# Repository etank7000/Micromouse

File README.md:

# Micromouse
UCLA IEEE Micromouse 2017-2018

To get the arm toolchain used in this repo, check out the following link and download the appropriate tar file. Be sure to read the included readme in the tar file as well.

https://developer.arm.com/open-source/gnu-toolchain/gnu-rm/downloads/7-2017-q4-major-1-1

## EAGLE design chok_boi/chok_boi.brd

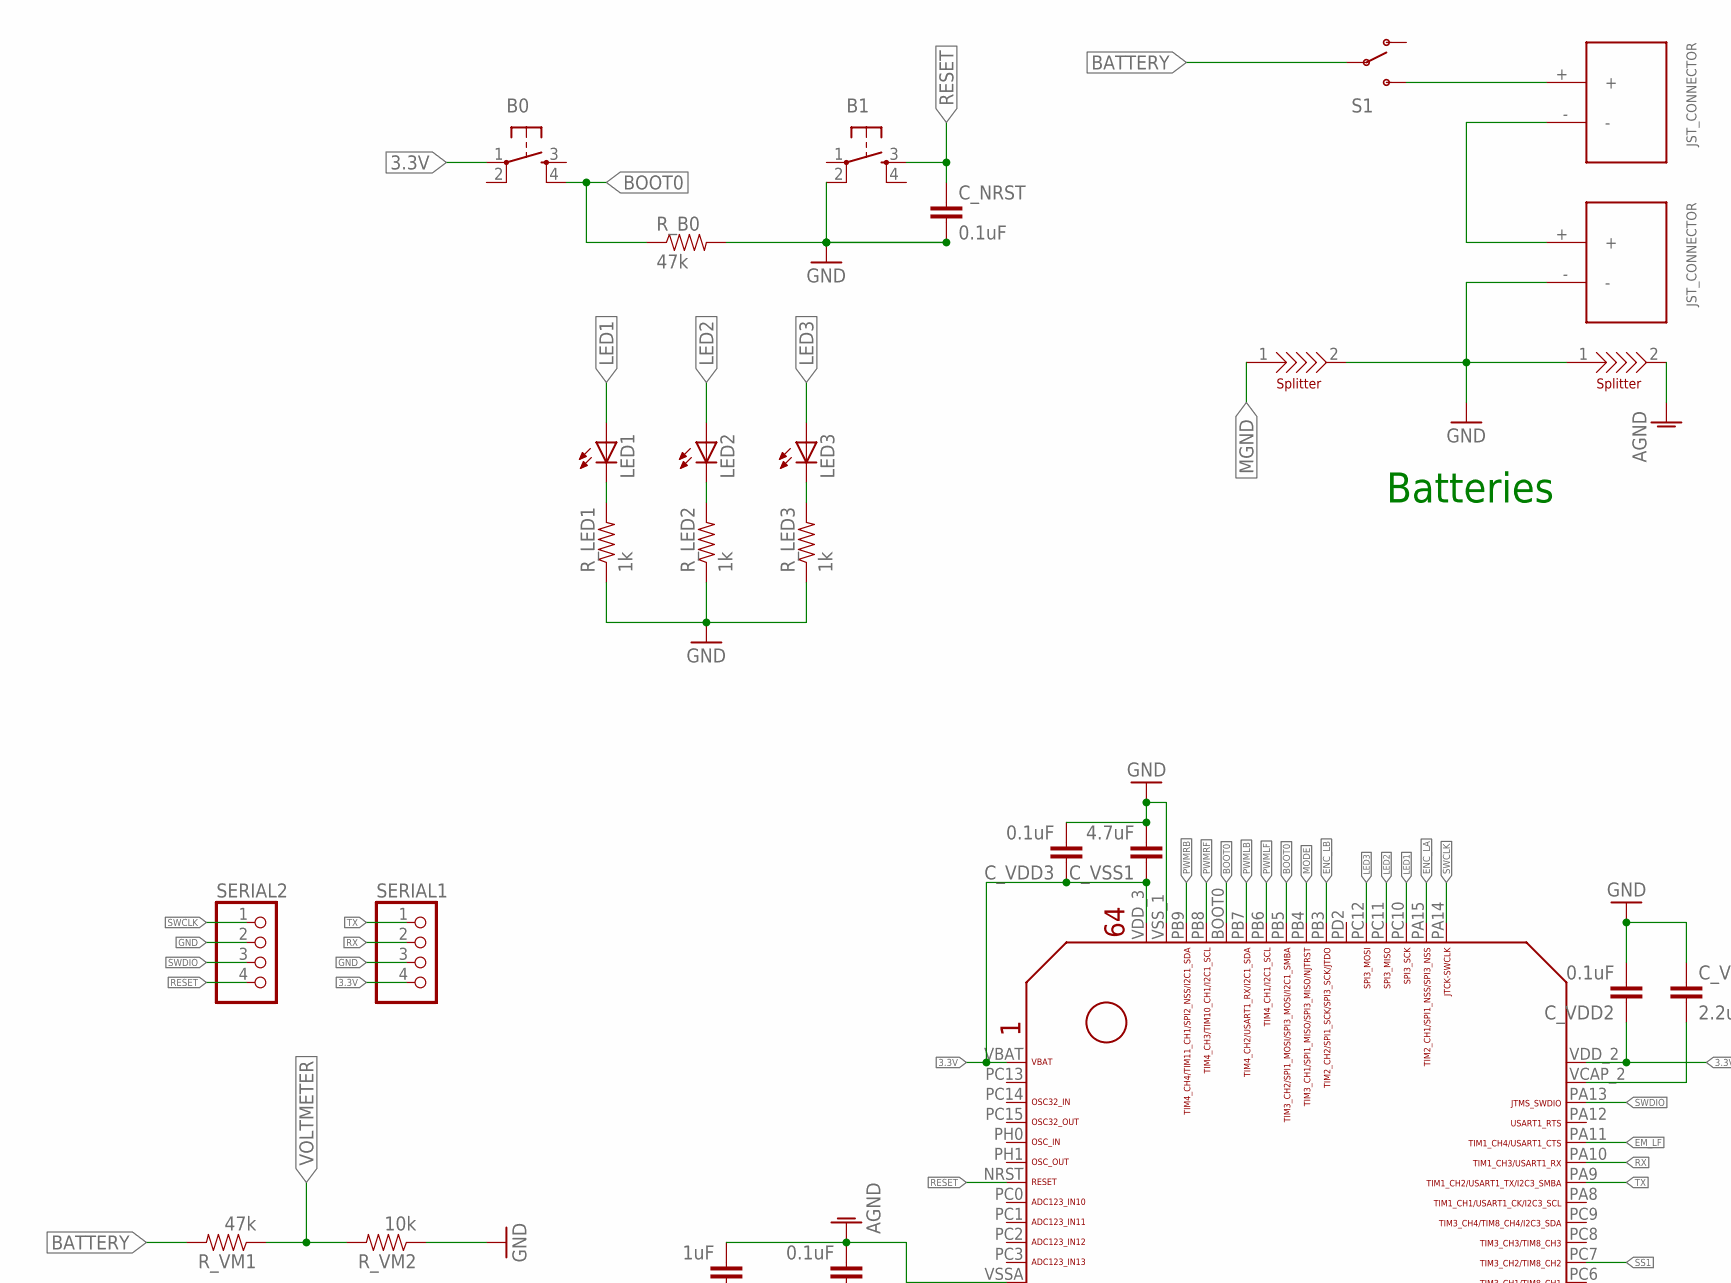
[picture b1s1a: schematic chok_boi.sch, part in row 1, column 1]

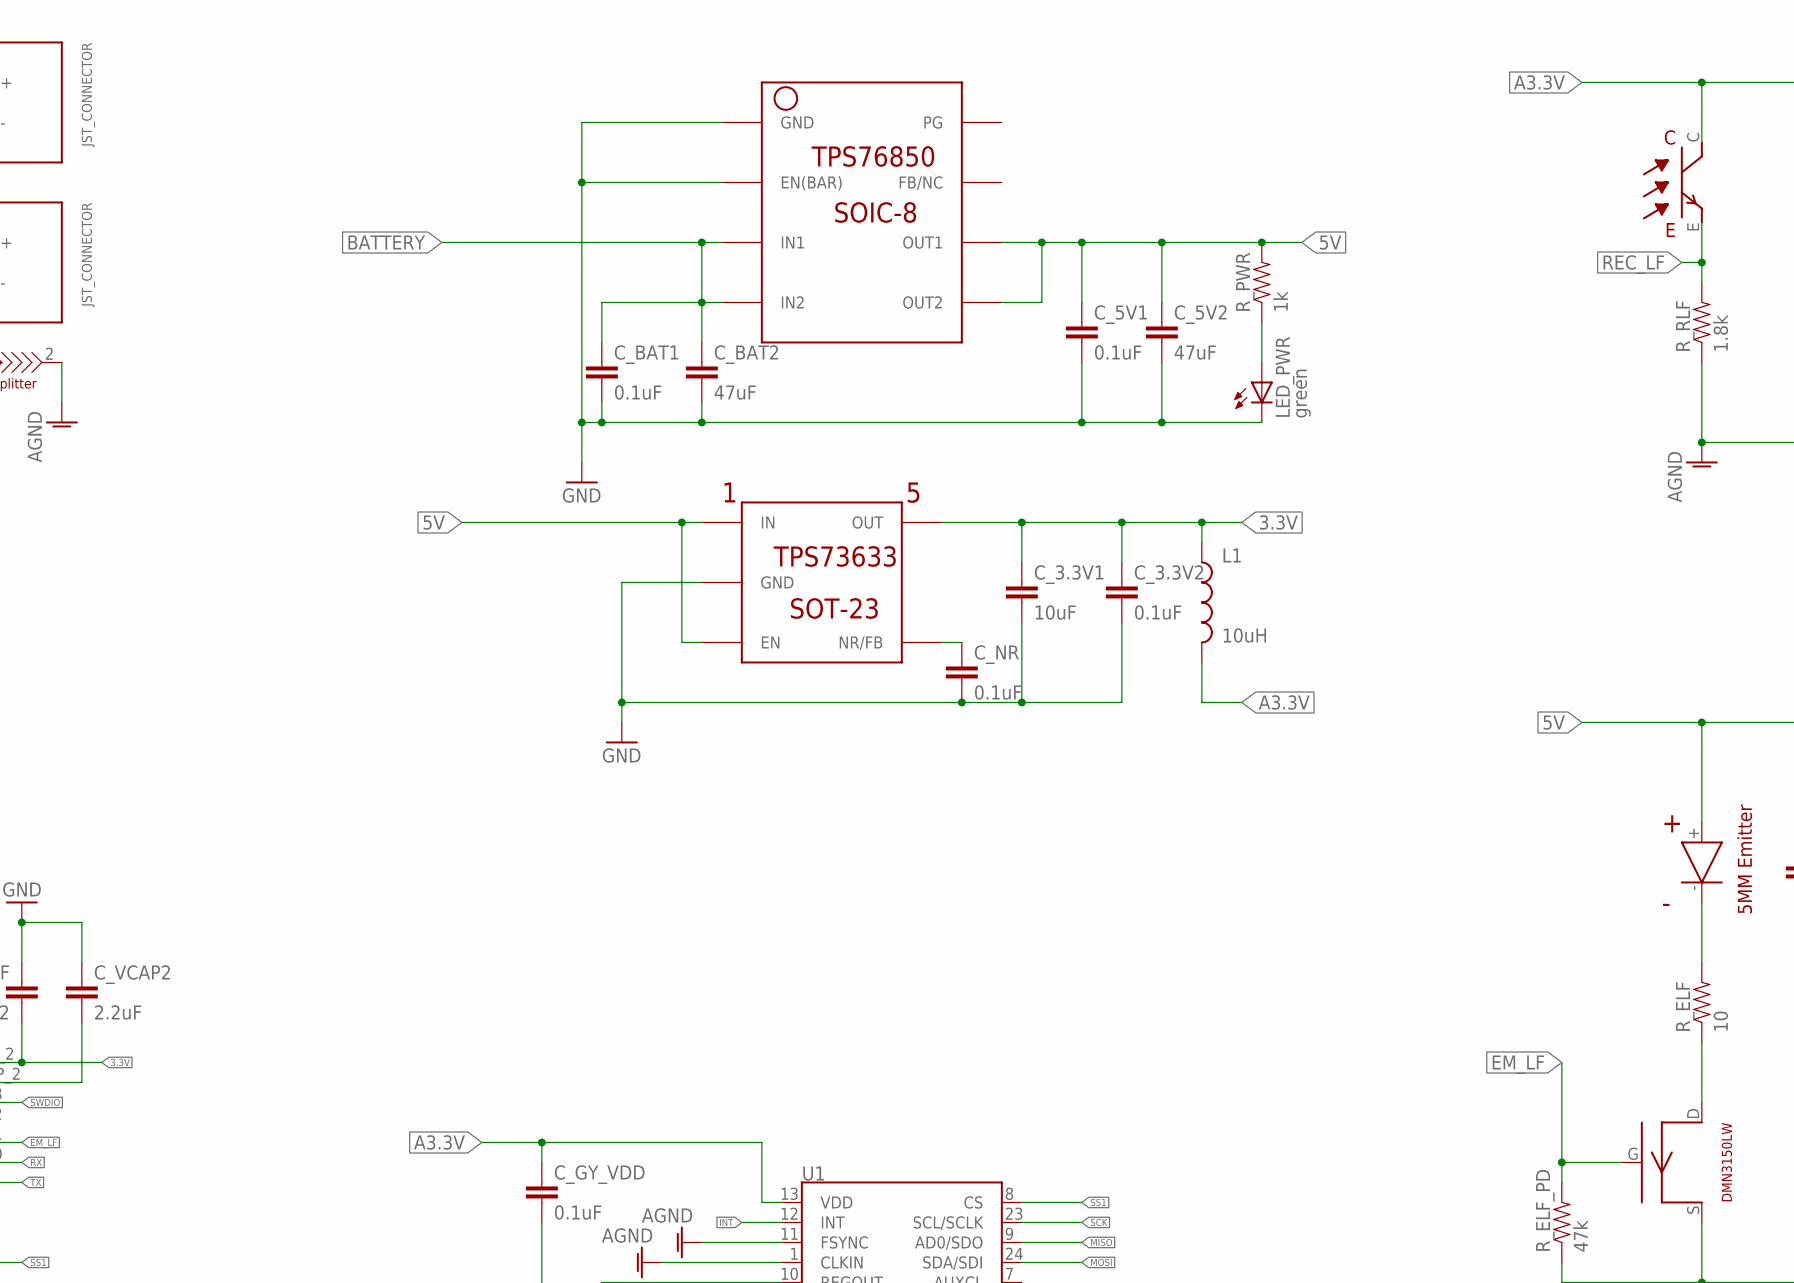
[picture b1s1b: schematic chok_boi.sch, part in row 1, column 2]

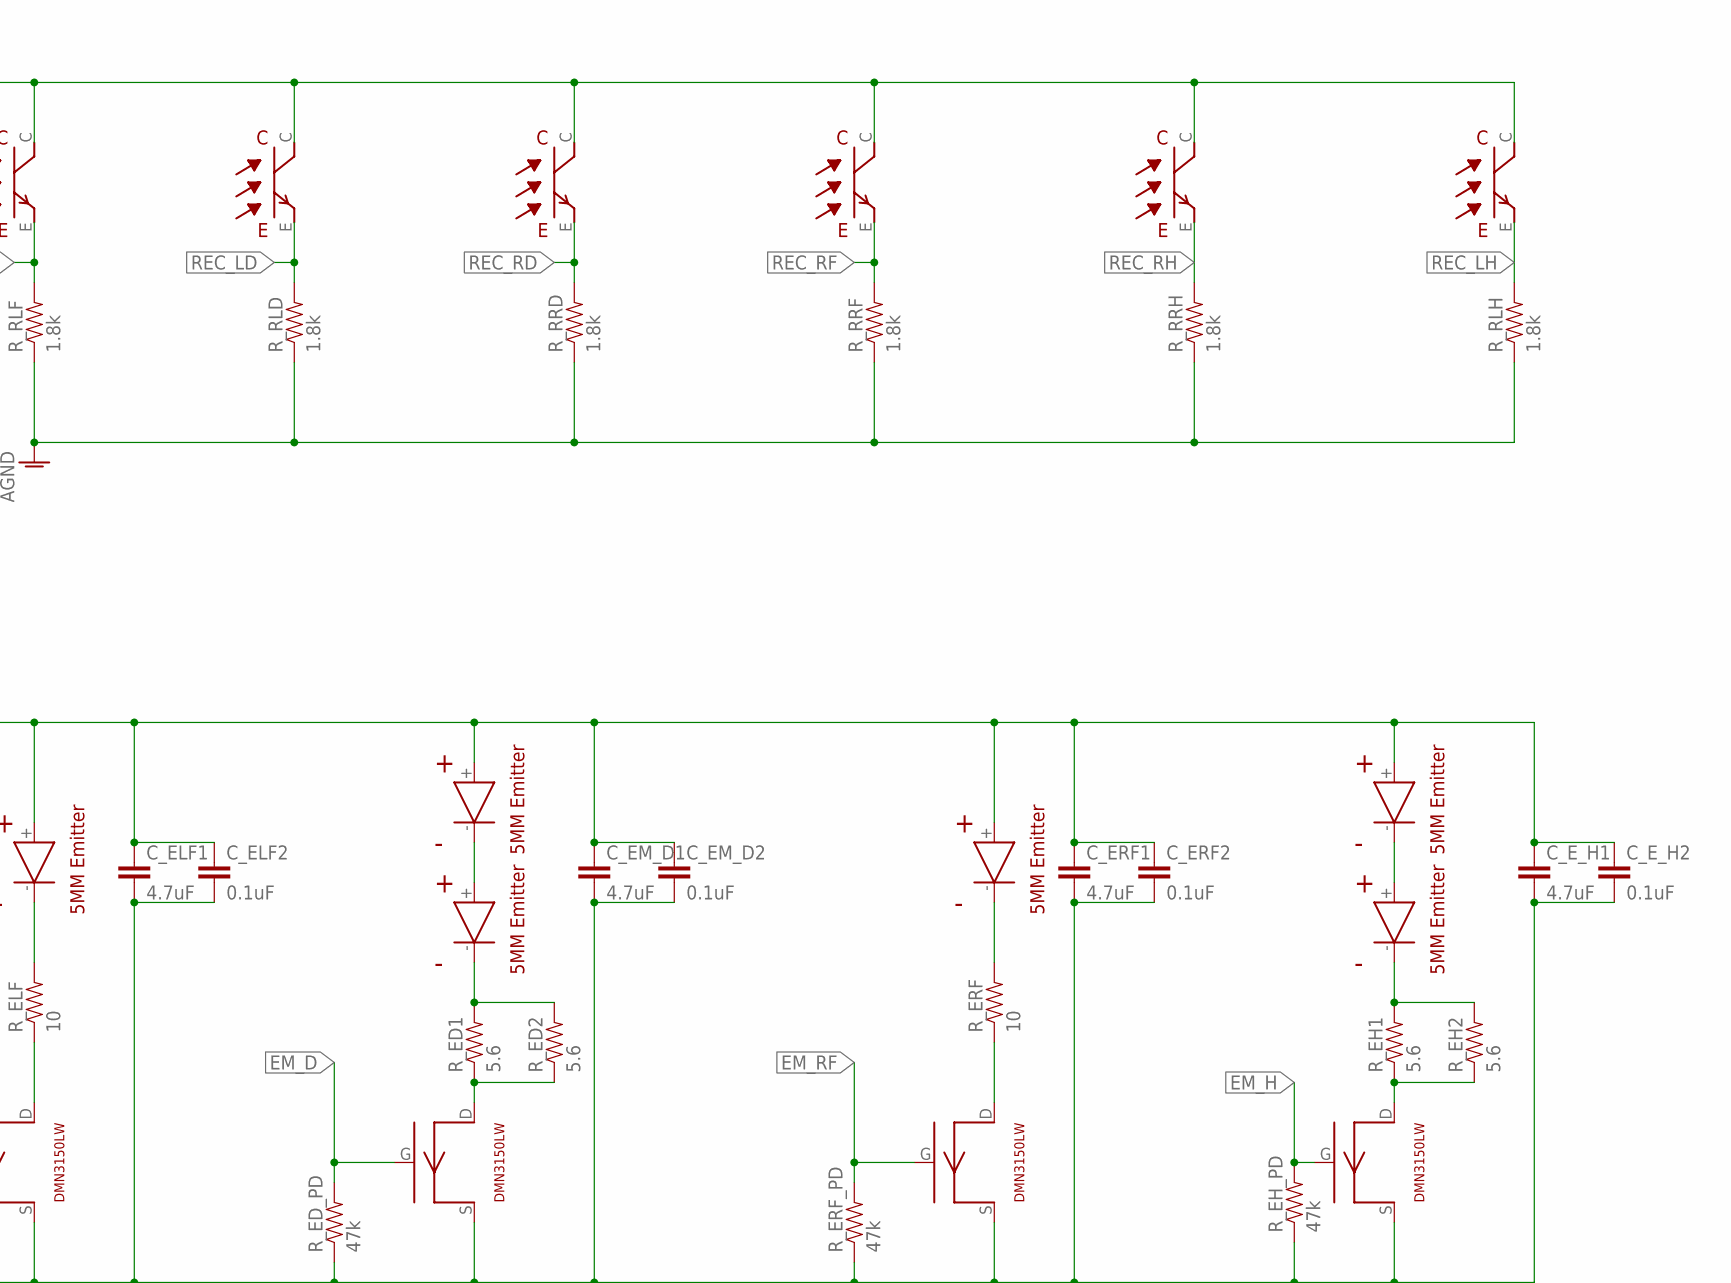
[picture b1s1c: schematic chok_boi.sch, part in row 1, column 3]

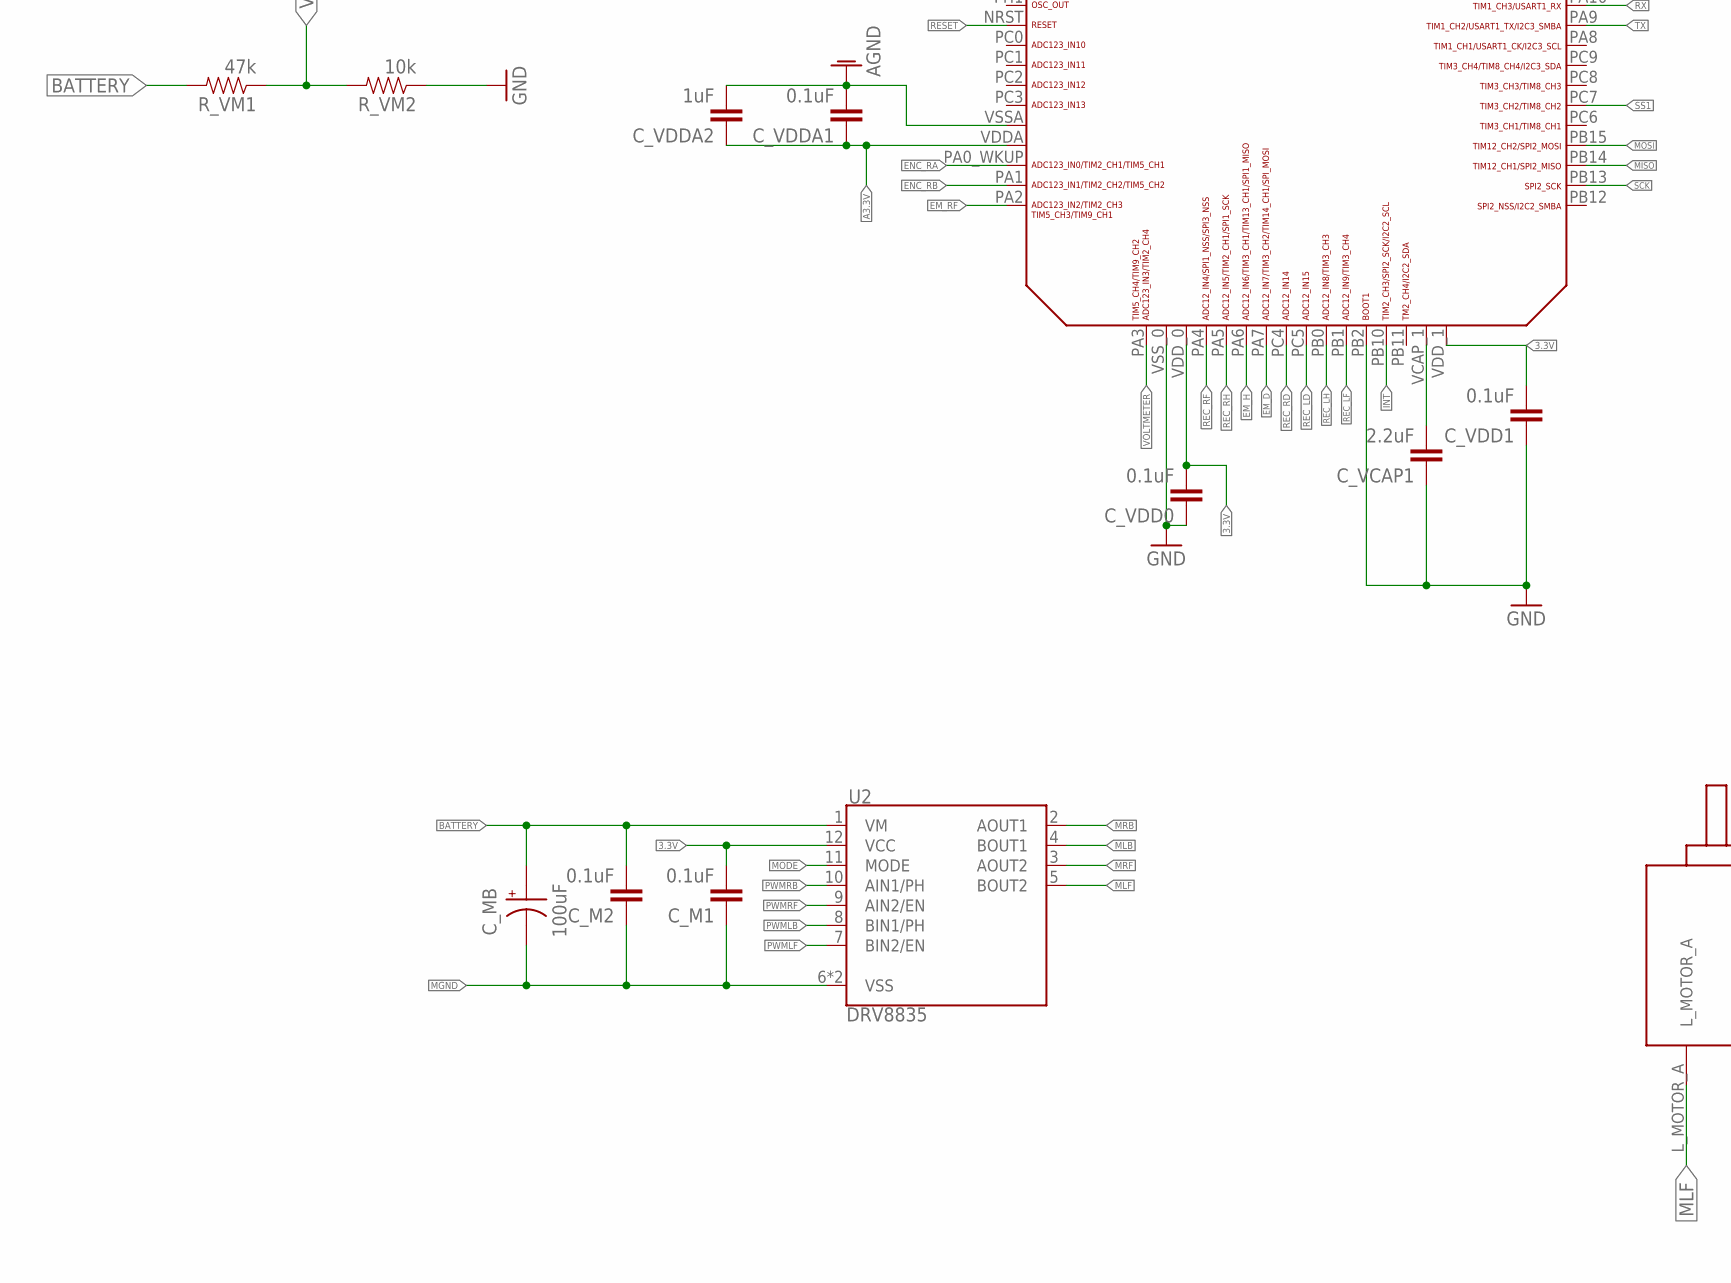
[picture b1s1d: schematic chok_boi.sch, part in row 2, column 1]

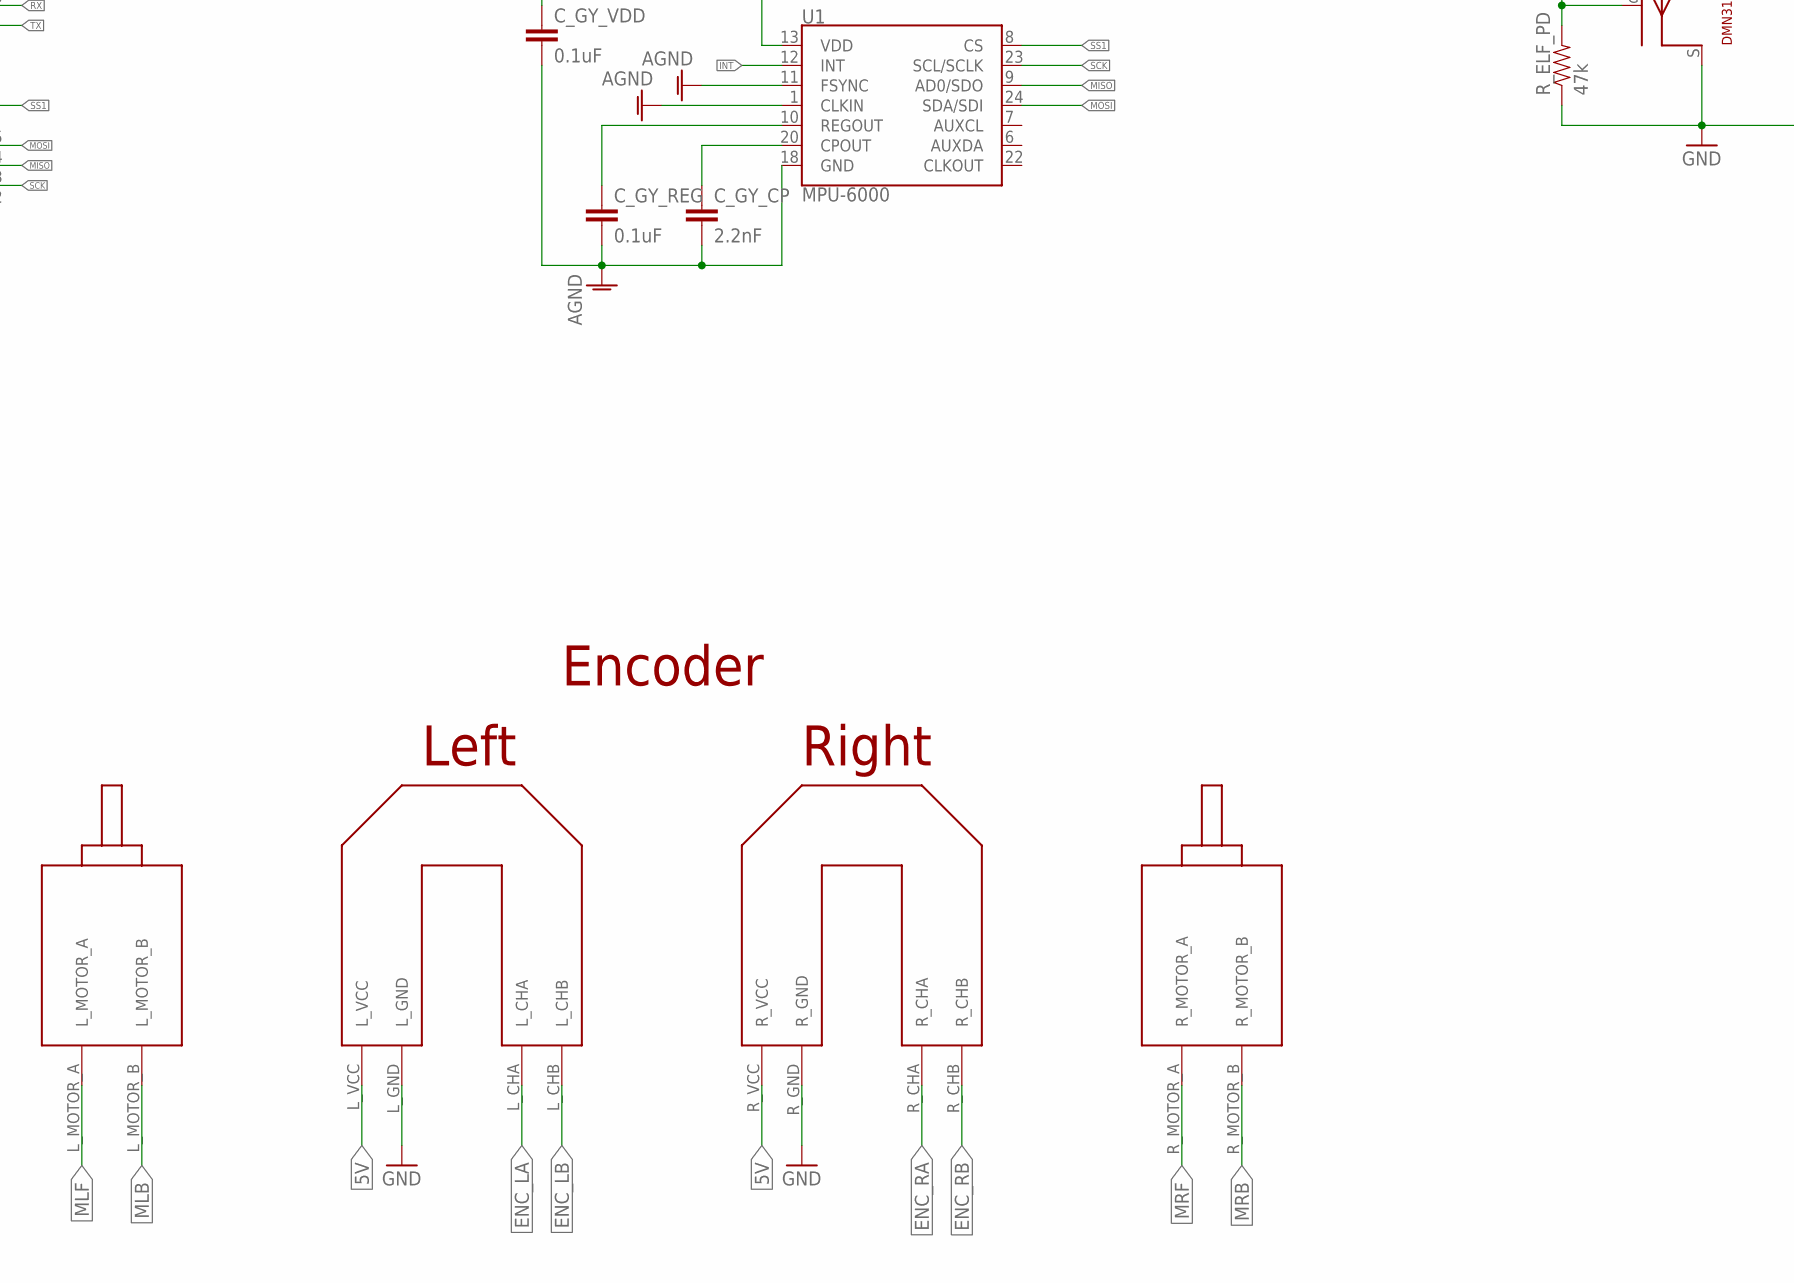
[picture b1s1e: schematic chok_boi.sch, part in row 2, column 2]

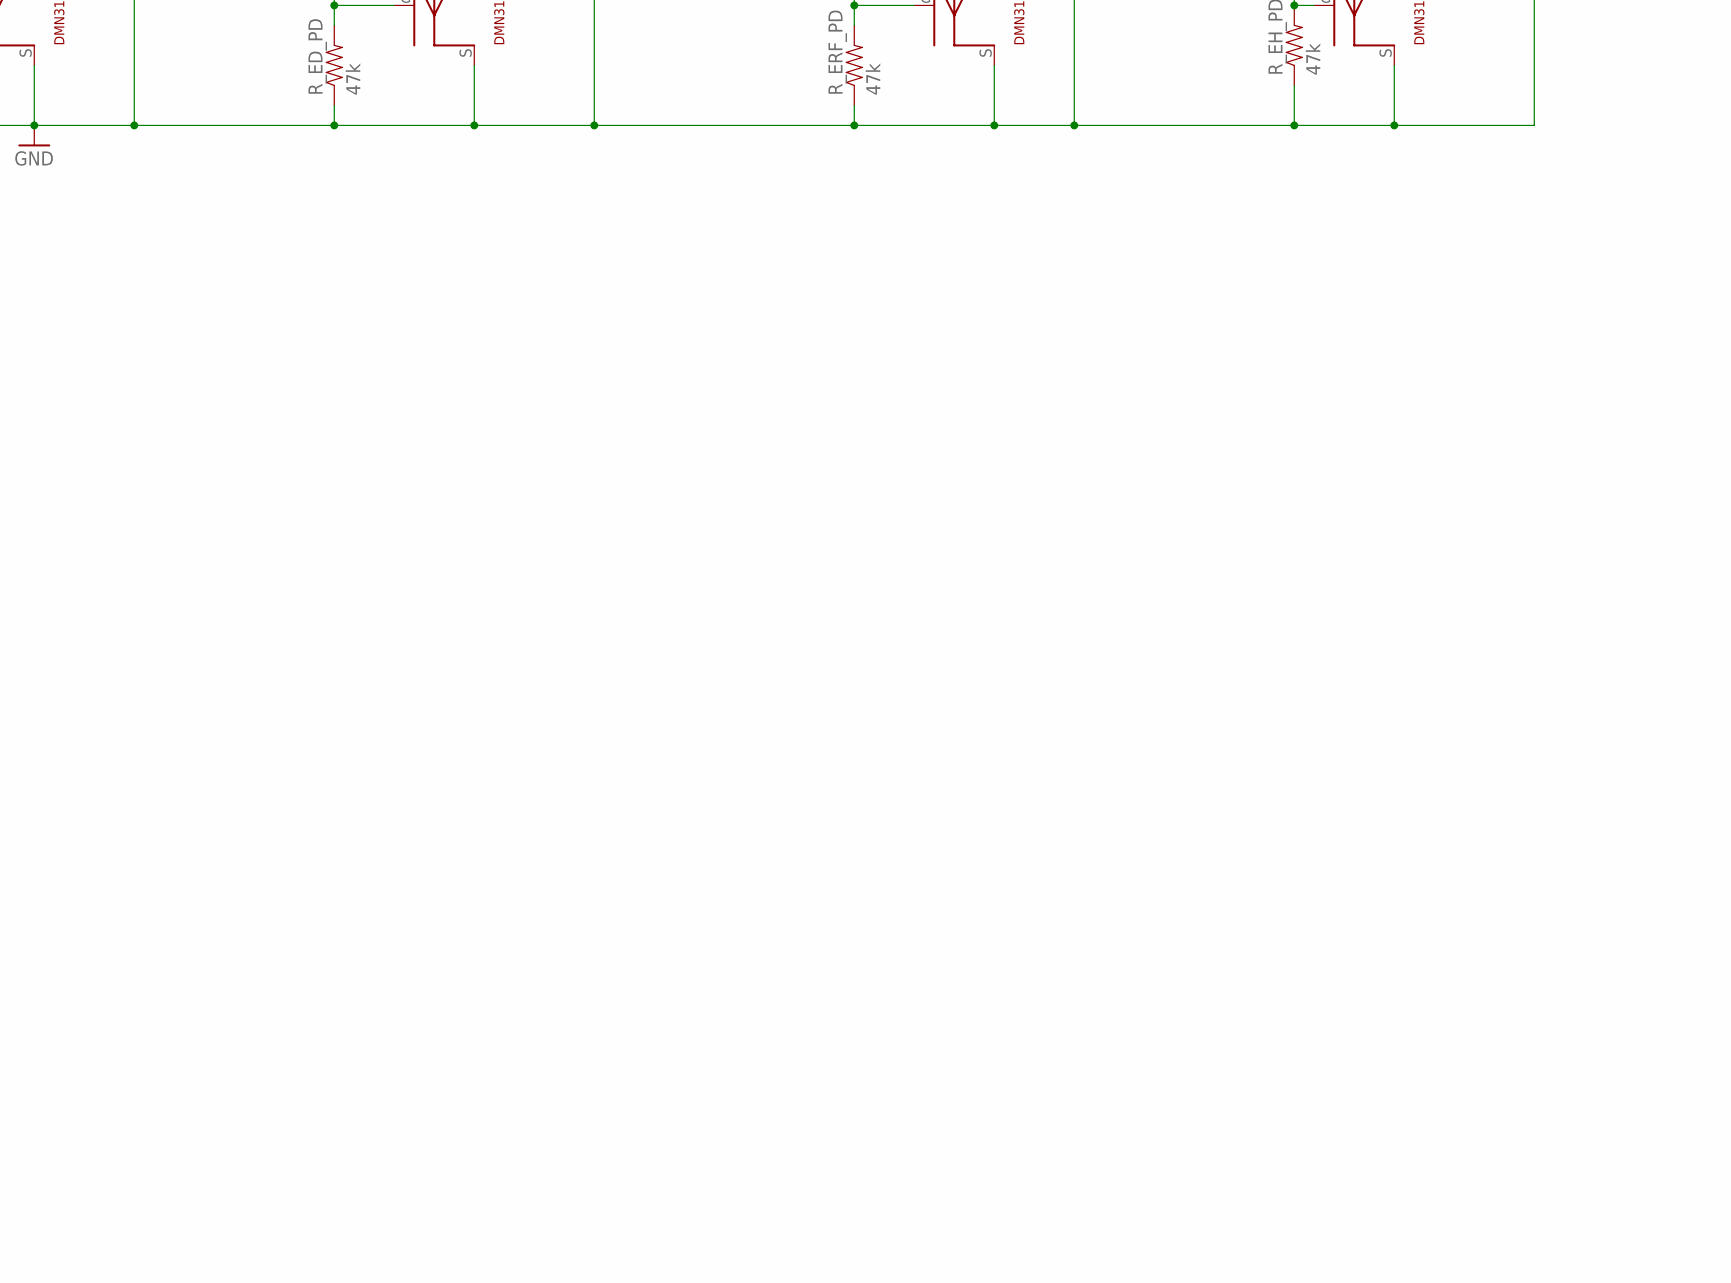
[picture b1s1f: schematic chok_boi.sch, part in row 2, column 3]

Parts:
B0, B1: TAC_SWITCHSMD; TACTILE-SWITCH-SMD
C_3.3V1: 10uF; 0603-CAP
C_3.3V2, C_5V1: 0.1uF; 0603-CAP
C_5V2: 47uF; 1210
C_BAT1: 0.1uF; 0603-CAP
C_BAT2: 47uF; 1210
C_ELF1: 4.7uF; 0603-CAP
C_ELF2: 0.1uF; 0603-CAP
C_EM_D1: 4.7uF; 0603-CAP
C_EM_D2: 0.1uF; 0603-CAP
C_ERF1: 4.7uF; 0603-CAP
C_ERF2: 0.1uF; 0603-CAP
C_E_H1: 4.7uF; 0603-CAP
C_E_H2: 0.1uF; 0603-CAP
C_GY_CP: 2.2nF; 0603-CAP
C_GY_REG: 0.1uF; 0603-CAP
C_GY_VDD: 0.1uF; 0603-CAP
C_M1, C_M2: 0.1uF; 0603-CAP
C_MB: 100uF; X
C_NR: 0.1uF; 0603-CAP
C_NRST: 0.1uF; 0603-CAP
C_VCAP1, C_VCAP2: 2.2uF; 0603-CAP
C_VDD0, C_VDD1, C_VDD2, C_VDD3: 0.1uF; 0603-CAP
C_VDDA1: 0.1uF; 0603-CAP
C_VDDA2: 1uF; 0603-CAP
C_VSS1: 4.7uF; 0603-CAP
L1: 10uH; 1007
LED1, LED2, LED3: LED0603; LED-0603
LED_PWR: green; LED-1206
LEFT_FRONT_EMITTER: EMITTER
NMOS1, NMOS2, NMOS3, NMOS4: DMN3150LW
REC_LF: RECEIVER
R_B0: 47k; 0603-RES
R_ED1, R_ED2: 5.6; 0603-RES
R_ED_PD: 47k; 0603-RES
R_EH1, R_EH2: 5.6; 0603-RES
R_EH_PD: 47k; 0603-RES
R_ELF: 10; 0603-RES
R_ELF_PD: 47k; 0603-RES
R_ERF: 10; 0603-RES
R_ERF_PD: 47k; 0603-RES
R_LED1, R_LED2, R_LED3: 1k; 0603-RES
R_PWR: 1k; 0603-RES
R_RLD: 1.8k; 0603-RES
R_RLF: 1.8k; 0603-RES
R_RLH: 1.8k; 0603-RES
R_RRD: 1.8k; 0603-RES
R_RRF: 1.8k; 0603-RES
R_RRH: 1.8k; 0603-RES
R_VM1: 47k; 0603-RES
R_VM2: 10k; 0603-RES
S1: SWITCH-SPSTPTH; SWITCH-SPDT
SERIAL1, SERIAL2: PINHD-1X4; 1X04
U1: MPU-6000; QFN-24-EP
U2: DRV8835; WSON-12
U$1, U$2: JST_CONNECTOR_FEMALE
U$3: TPS73633(SOT-23)
U$4: TPS76850(SOIC-8)
U$5: STM32F405/415_LQFP64
U$7, U$8, U$9, U$20, U$21: RECEIVER
U$11, U$13, U$17, U$18, U$19: EMITTER
U$12: FUTURA_V1.0_MOTOR_MOUNT; FUTURA_V1.0_MOTOT_MOUNT
U$15, U$16: SPLITTER

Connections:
3.3V: B0.1, C_3.3V1.1, C_3.3V2.1, C_M1.2, C_VDD0.2, C_VDD1.2, C_VDD2.1, C_VDD3.1, C_VSS1.1, L1.1, SERIAL1.4, U2.12 (VCC), U$3.OUT, U$5.VBAT, U$5.VDD_0, U$5.VDD_1, U$5.VDD_2, U$5.VDD_3
5V: C_5V1.1, C_5V2.1, C_ELF1.1, C_ELF2.1, C_EM_D1.1, C_EM_D2.1, C_ERF1.1, C_ERF2.1, C_E_H1.1, C_E_H2.1, LEFT_FRONT_EMITTER.+, R_PWR.2, U$3.EN, U$3.IN, U$4.OUT1, U$4.OUT2, U$11.+, U$12.L_VCC, U$12.R_VCC, U$13.+, U$18.+
A3.3V: C_GY_VDD.1, C_VDDA1.1, C_VDDA2.1, L1.2, REC_LF.C, U1.13 (VDD), U$5.VDDA, U$7.C, U$8.C, U$9.C, U$20.C, U$21.C
AGND: C_GY_CP.2, C_GY_REG.2, C_GY_VDD.2, C_VDDA1.2, C_VDDA2.2, R_RLD.1, R_RLF.1, R_RLH.1, R_RRD.1, R_RRF.1, R_RRH.1, U1.1 (CLKIN), U1.11 (FSYNC), U1.18 (GND), U$5.VSSA, U$15.2
BATTERY: C_BAT1.1, C_BAT2.1, C_M2.2, C_MB.A, R_VM1.2, S1.2, U2.1 (VM), U$4.IN1, U$4.IN2
BOOT0: B0.4, R_B0.1, U$5.BOOT0, U$5.PB5
D2_EM: R_ED1.2, R_ED2.2, U$17.-
D_EM: U$11.-, U$17.+
EM_D: NMOS2.G, R_ED_PD.2, U$5.PA7
EM_H: NMOS4.G, R_EH_PD.2, U$5.PA6
EM_LF: NMOS1.G, R_ELF_PD.2, U$5.PA11
EM_RF: NMOS3.G, R_ERF_PD.2, U$5.PA2
ENC_LA: U$5.PA15, U$12.L_CHA
ENC_LB: U$5.PB3, U$12.L_CHB
ENC_RA: U$5.PA0_WKUP (PA0_AKUP), U$12.R_CHA
ENC_RB: U$5.PA1, U$12.R_CHB
GND: B1.2, C_3.3V1.2, C_3.3V2.2, C_5V1.2, C_5V2.2, C_BAT1.2, C_BAT2.2, C_ELF1.2, C_ELF2.2, C_EM_D1.2, C_EM_D2.2, C_ERF1.2, C_ERF2.2, C_E_H1.2, C_E_H2.2, C_NR.2, C_NRST.2, C_VCAP1.1, C_VCAP2.1, C_VDD0.1, C_VDD1.1, C_VDD2.2, C_VDD3.2, C_VSS1.2, LED_PWR.C, NMOS1.S, NMOS2.S, NMOS3.S, NMOS4.S, R_B0.2, R_ED_PD.1, R_EH_PD.1, R_ELF_PD.1, R_ERF_PD.1, R_LED1.1, R_LED2.1, R_LED3.1, R_VM2.1, SERIAL1.3, SERIAL2.2, U$1.-, U$3.GND, U$4.EN(BAR), U$4.GND, U$5.PB2, U$5.VSS_0, U$5.VSS_1, U$12.L_GND, U$12.R_GND, U$15.1, U$16.2
H2_EM: R_EH1.2, R_EH2.2, U$19.-
H_EM: U$18.-, U$19.+
INT: U1.12 (INT), U$5.PB10
LED1: LED1.A, U$5.PC10
LED2: LED2.A, U$5.PC11
LED3: LED3.A, U$5.PC12
LF_EM: LEFT_FRONT_EMITTER.-, R_ELF.2
MGND: C_M1.1, C_M2.1, C_MB.C, U2.6 (VSS), U2.PAD (VSS), U$16.1
MISO: U1.9 (AD0/SDO), U$5.PB14
MLB: U2.4 (BOUT1), U$12.L_MOTOR_B
MLF: U2.5 (BOUT2), U$12.L_MOTOR_A
MODE: U2.11 (MODE), U$5.PB4
MOSI: U1.24 (SDA/SDI), U$5.PB15
MRB: U2.2 (AOUT1), U$12.R_MOTOR_B
MRF: U2.3 (AOUT2), U$12.R_MOTOR_A
unnamed: U$1.+, U$2.-
unnamed: S1.3 (S), U$2.+
unnamed: C_NR.1, U$3.NR/FB
unnamed: C_VCAP1.2, U$5.VCAP_1
unnamed: NMOS3.D, R_ERF.1
unnamed: C_VCAP2.2, U$5.VCAP_2
unnamed: NMOS1.D, R_ELF.1
unnamed: LED_PWR.A, R_PWR.1
unnamed: LED1.C, R_LED1.2
unnamed: LED2.C, R_LED2.2
unnamed: NMOS2.D, R_ED1.1, R_ED2.1
unnamed: NMOS4.D, R_EH1.1, R_EH2.1
unnamed: C_GY_REG.1, U1.10 (REGOUT)
unnamed: LED3.C, R_LED3.2
unnamed: C_GY_CP.1, U1.20 (CPOUT)
PWMLB: U2.8 (BIN1/PH), U$5.PB7
PWMLF: U2.7 (BIN2/EN), U$5.PB6
PWMRB: U2.10 (AIN1/PH), U$5.PB9
PWMRF: U2.9 (AIN2/EN), U$5.PB8
REC_LD: R_RLD.2, U$5.PC5, U$7.E
REC_LF: REC_LF.E, R_RLF.2, U$5.PB1
REC_LH: R_RLH.2, U$5.PB0, U$21.E
REC_RD: R_RRD.2, U$5.PC4, U$8.E
REC_RF: R_RRF.2, U$5.PA4, U$9.E
REC_RH: R_RRH.2, U$5.PA5, U$20.E
RESET: B1.3, C_NRST.1, SERIAL2.4, U$5.NRST
RF_EM: R_ERF.2, U$13.-
RX: SERIAL1.2, U$5.PA10
SCK: U1.23 (SCL/SCLK), U$5.PB13
SS1: U1.8 (CS), U$5.PC7
SWCLK: SERIAL2.1, U$5.PA14
SWDIO: SERIAL2.3, U$5.PA13
TX: SERIAL1.1, U$5.PA9
VOLTMETER: R_VM1.1, R_VM2.2, U$5.PA3

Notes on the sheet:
Batteries

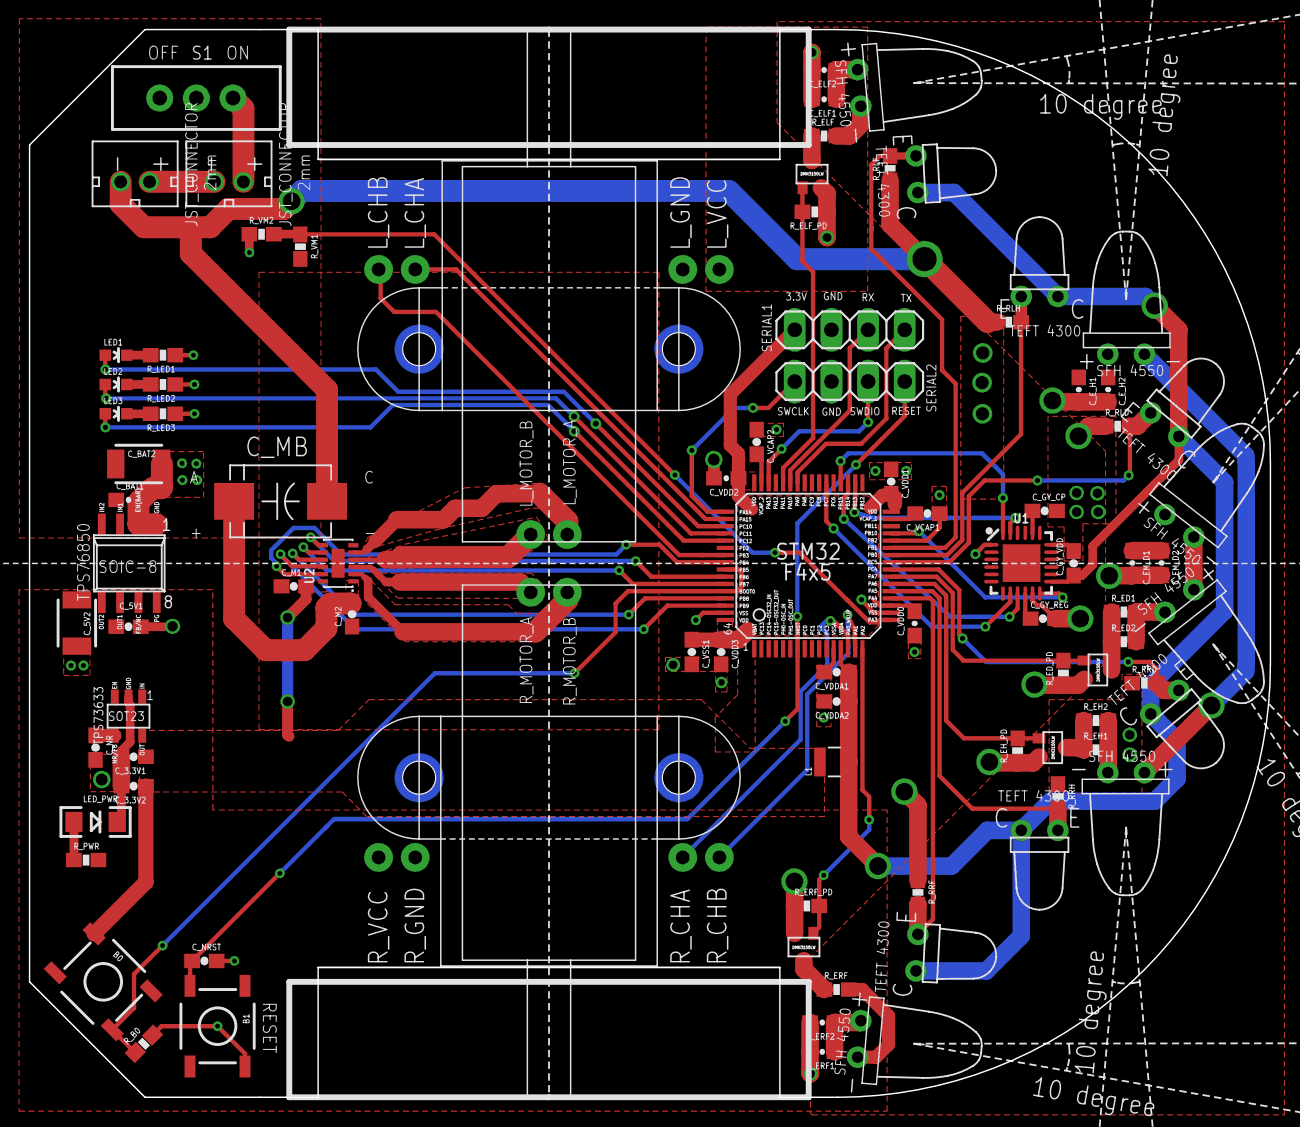
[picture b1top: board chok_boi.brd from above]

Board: 2 copper layers, 86.0 x 74.0 mm, 90 parts (0 on the bottom side), 66 nets.

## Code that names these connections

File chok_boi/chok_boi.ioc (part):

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Mcu.Name=STM32F405RGTx
Mcu.Package=LQFP64
Mcu.UserName=STM32F405RGTx
PA0-WKUP.GPIOParameters=GPIO_Label
PA0-WKUP.GPIO_Label=ENC_RA
PA0-WKUP.Signal=S_TIM5_CH1
PA1.GPIOParameters=GPIO_Label
PA1.GPIO_Label=ENC_RB
PA1.Signal=S_TIM5_CH2
PA10.Mode=Asynchronous
PA10.Signal=USART1_RX
PA11.GPIOParameters=GPIO_Label
PA11.GPIO_Label=EM_LF
PA11.Signal=GPIO_Output
PA13.Mode=Serial_Wire
PA13.Signal=SYS_JTMS-SWDIO
PA14.Mode=Serial_Wire
PA14.Signal=SYS_JTCK-SWCLK
PA15.GPIOParameters=GPIO_Label
PA15.GPIO_Label=ENC_LA
PA15.Signal=S_TIM2_CH1_ETR
PA2.GPIOParameters=GPIO_Label
PA2.GPIO_Label=EM_RF
PA2.Signal=GPIO_Output
PA3.GPIOParameters=GPIO_Label
PA3.GPIO_Label=VOLTMETER
PA3.Signal=ADCx_IN3
PA4.GPIOParameters=GPIO_Label
PA4.GPIO_Label=REC_RF
PA4.Signal=ADCx_IN4
PA5.GPIOParameters=GPIO_Label
PA5.GPIO_Label=REC_RH
PA5.Signal=ADCx_IN5
PA6.GPIOParameters=GPIO_Label
PA6.GPIO_Label=EM_H
PA6.Signal=GPIO_Output
PA7.GPIOParameters=GPIO_Label
PA7.GPIO_Label=EM_D
PA7.Signal=GPIO_Output
PA9.Mode=Asynchronous
PA9.Signal=USART1_TX
PB0.GPIOParameters=GPIO_Label
PB0.GPIO_Label=REC_LH
PB0.Signal=ADCx_IN8
PB1.GPIOParameters=GPIO_Label
PB1.GPIO_Label=REC_LF
PB1.Signal=ADCx_IN9
PB10.GPIOParameters=GPIO_Label
PB10.GPIO_Label=INT
PB10.Signal=GPXTI10
PB13.Mode=Full_Duplex_Master
PB13.Signal=SPI2_SCK
PB14.Mode=Full_Duplex_Master
PB14.Signal=SPI2_MISO
PB15.Mode=Full_Duplex_Master
PB15.Signal=SPI2_MOSI
PB3.GPIOParameters=GPIO_Label
PB3.GPIO_Label=ENC_LB
PB3.Signal=S_TIM2_CH2
PB4.GPIOParameters=GPIO_Label
PB4.GPIO_Label=MODE
PB4.Signal=GPIO_Output
PB5.GPIOParameters=GPIO_Label
PB5.GPIO_Label=BOOT0
PB5.Signal=GPXTI5
PB6.Signal=S_TIM4_CH1
PB7.GPIOParameters=GPIO_Label
PB7.GPIO_Label=PH_L
PB7.Signal=GPIO_Output
PB8.Signal=S_TIM4_CH3
PB9.GPIOParameters=GPIO_Label
PB9.GPIO_Label=PH_R
PB9.Signal=GPIO_Output
PC10.GPIOParameters=GPIO_Label
PC10.GPIO_Label=LED1
PC10.Signal=GPIO_Output
PC11.GPIOParameters=GPIO_Label
PC11.GPIO_Label=LED2
PC11.Signal=GPIO_Output
PC12.GPIOParameters=GPIO_Label
PC12.GPIO_Label=LED3
PC12.Signal=GPIO_Output
PC4.GPIOParameters=GPIO_Label
PC4.GPIO_Label=REC_RD
PC4.Signal=ADCx_IN14
PC5.GPIOParameters=GPIO_Label
PC5.GPIO_Label=REC_LD
PC5.Signal=ADCx_IN15
PC7.GPIOParameters=PinState,GPIO_Label
PC7.GPIO_Label=SS1
PC7.PinState=GPIO_PIN_SET
PC7.Signal=GPIO_Output
RCC.HSE_VALUE=25000000
RCC.SYSCLKFreq_VALUE=168000000
RCC.SYSCLKSource=RCC_SYSCLKSOURCE_PLLCLK
board=chok_boi

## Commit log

2017-09-30 Add files
2017-11-10 add power system
2017-11-18 Add gyro and update MOSFETS
2017-11-21 Add gitignore and finish gyro connections
2017-11-21 Add datasheet
2017-11-21 Finish rec/led pair schematic
2017-11-22 Start board
2017-11-22 Place all big components on board
2017-11-22 Add power and gnd planes
2017-11-22 Change part names for easier routing
2017-11-22 Finish component placement. Start routing
2017-11-22 117 Airwires Left
2017-11-23 Add DRV8835 motor driver
2017-11-23 Add bypass caps to DRV8835
2017-11-25 Add cell outline
2017-11-25 Improve upper half board placement
2017-11-26 Modify polygons to reduce routes. 79 airwires left
2017-11-26 74 airwires left
2017-11-27 In middle of reworking traces
2017-11-29 More routing
2017-11-30 Move LEDs on MCU and route more. 22 airwires left
2017-11-30 No more airwires!
2017-11-30 Move Vias further back from MCU
2017-12-01 Finish routing
2017-12-01 Make MGND larger
2017-12-01 Design review fixes
2017-12-01 Add text to PCB and change values of 2 passives
2017-12-15 Add peripheral code
2017-12-16 Add code for motors, encoders, and IR sensors
2017-12-16 Move files around
2017-12-22 Update sensor code and add stack implementation
2017-12-22 Add Doxygen documentation
2017-12-30 Add controller and debugging interface
2018-01-26 Update stuff
2018-01-30 Read MPU6000 whoami
2018-02-20 Reorganize directories and add gyro code
2018-03-23 Add straight movement
2018-04-05 Start gyro changes
2018-04-20 Implement curve turn and fix diagonal IR sensors
2018-04-29 Implement FloodFill and add comments to various places
2018-04-30 Fix BitVector256 bug and test FloodFill
2018-05-19 Add adjuster for stops
2018-05-20 2 AM pre AAMC build
2018-05-20 6 aM pre AAMC working code
2018-05-21 AAMC official runs
2018-05-26 Reverse floodfill to go from center to start of maze
2018-05-27 Fix flood fill bug and test for CAMM overnight build session
2018-05-27 Working gyro code, must account for drift now!
2018-05-28 CAMM official runs
2019-03-01 Add mac flash and makefile
2019-04-20 Start gyro work again
2019-04-27 Gyro scope working, left turn seems to be generally accurate(90degree +- 5) but right turn is bad (90 degree +- 25)
2019-05-03 Add comments and fix variable name in main.c
2019-05-05 UCR comp, pre 16x16 maze code
2019-05-06 Final UCR Comp - 40s completion
2019-05-11 Fix curve turns and implement turns using gyros, TODO: 180s with gyro
2019-05-26 Add turning with gyro
2019-05-26 Pre AAMC code
2019-05-26 AAMC morning of code - Remove curve turns and do with or without gyro turns
2019-05-26 AAMC code - 2nd Place
2019-06-02 Overnight CAMM code
2019-06-03 Final camm code - 1st place 12 seconds with curve turns

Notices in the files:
parts and their libraries:
SparkFun-Retired: Licensing:Creative Commons ShareAlike 4.0 International - https://creativecommons.org/licenses/by-sa/4.0
SparkFun: Licensing: CC v3.0 Share-Alike You are welcome to use this library for commercial purposes.
